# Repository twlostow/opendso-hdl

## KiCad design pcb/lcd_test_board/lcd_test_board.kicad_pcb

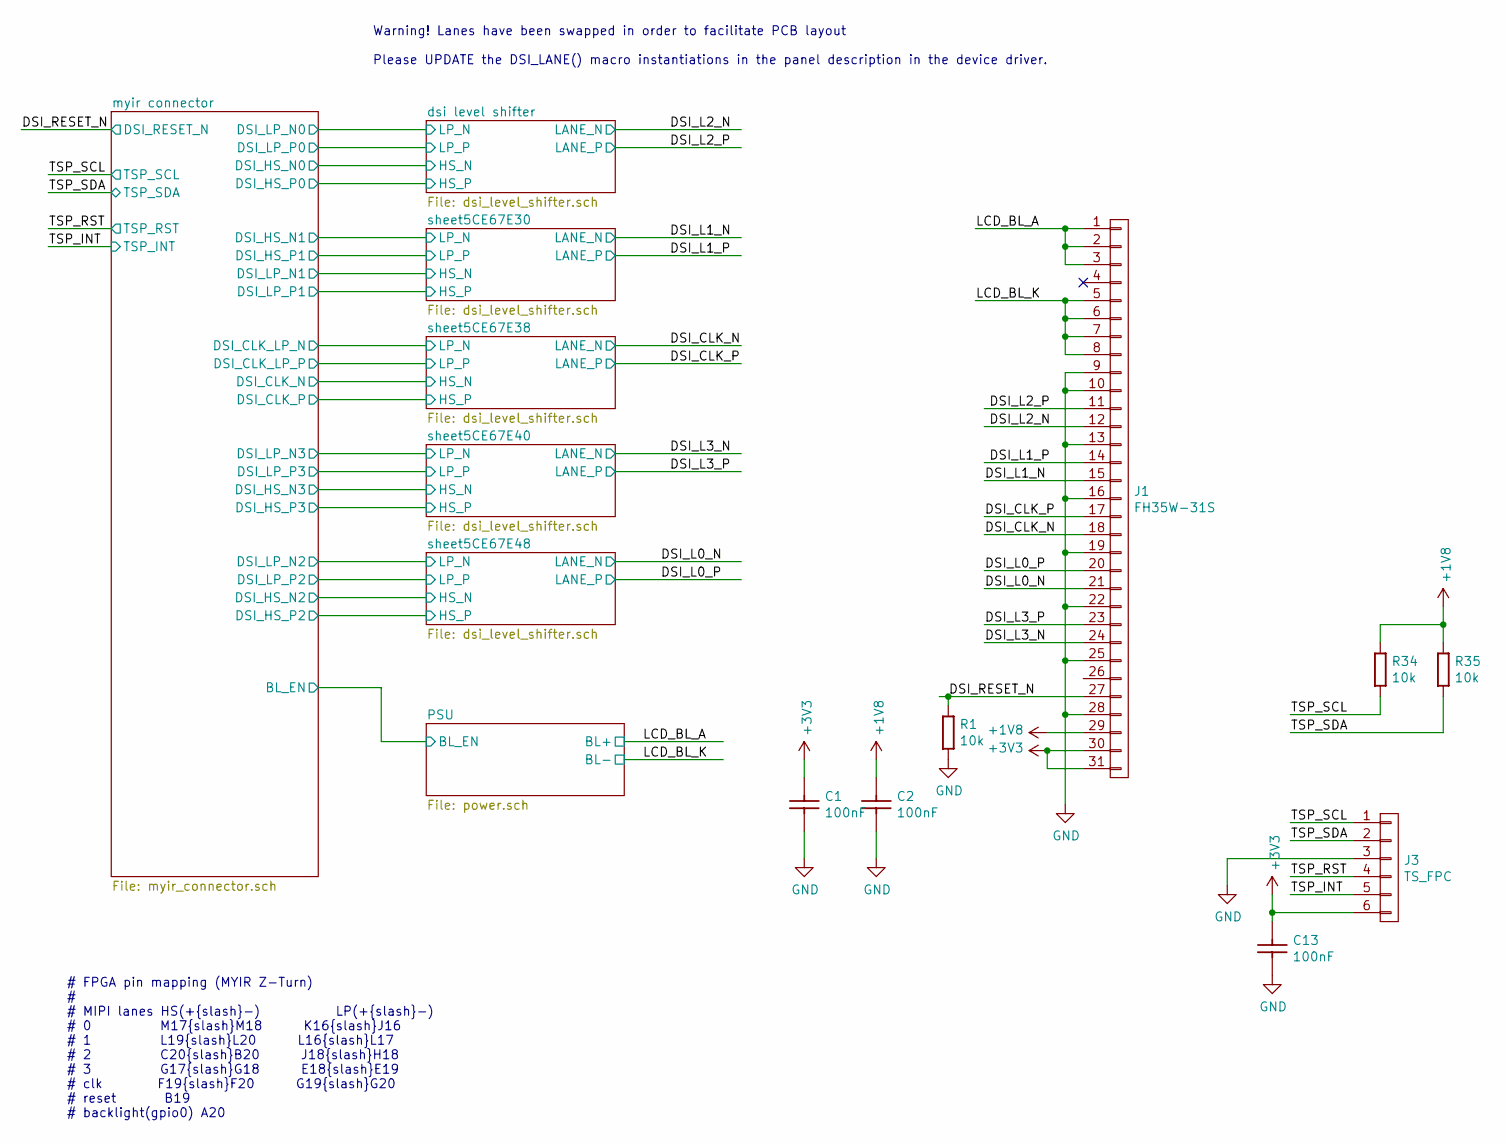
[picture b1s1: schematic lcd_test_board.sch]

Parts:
C1, C2, C13: CC0603_100NF_50V_10%_X5R; CAPC1608X87N; Voltage 50V; Tolerance ±10%; Part Number CC0603_100NF_50V_10%_X5R
J1: FH35W-31S
J3: TS_FPC; GT911_TS_FFC
R1, R34, R35: R0603_10K_1%_0.1W_100PPM; RESC1608X55N; Tolerance ±1%; Part Number R0603_10K_1%_0.1W_100PPM

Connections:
+1V8: C2.1, J1.29, R34.1, R35.1; also elsewhere on the board
+3V3: C1.1, C13.1, J1.30, J1.31, J3.6; also elsewhere on the board
/DSI_CLK_N: J1.18; also elsewhere on the board
/DSI_CLK_P: J1.17; also elsewhere on the board
/DSI_L0_N: J1.21; also elsewhere on the board
/DSI_L0_P: J1.20; also elsewhere on the board
/DSI_L1_N: J1.15; also elsewhere on the board
/DSI_L1_P: J1.14; also elsewhere on the board
/DSI_L2_N: J1.12; also elsewhere on the board
/DSI_L2_P: J1.11; also elsewhere on the board
/DSI_L3_N: J1.24; also elsewhere on the board
/DSI_L3_P: J1.23; also elsewhere on the board
/DSI_RESET_N: J1.27, R1.1; also elsewhere on the board
/LCD_BL_A: J1.1, J1.2, J1.3; also elsewhere on the board
/LCD_BL_K: J1.5, J1.6, J1.7, J1.8; also elsewhere on the board
/TSP_INT: J3.5; also elsewhere on the board
/TSP_RST: J3.4; also elsewhere on the board
/TSP_SCL: J3.1, R34.2; also elsewhere on the board
/TSP_SDA: J3.2, R35.2; also elsewhere on the board
GND: C1.2, C2.2, C13.2, J1.9, J1.10, J1.13, J1.16, J1.19, J1.22, J1.25, J1.28, J3.3, R1.2; also elsewhere on the board

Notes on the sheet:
# FPGA pin mapping (MYIR Z-Turn) # # MIPI lanes HS(+{slash}-) LP(+{slash}-) # 0 M17{slash}M18 K16{slash}J16 # 1 L19{slash}L20 L16{slash}L17 # 2 C20{slash}B20 J18{slash}H18 # 3 G17{slash}G18 E18{slash}E19 # clk F19{slash}F20 G19{slash}G20 # reset B19 # backlight(gpio0) A20
Warning! Lanes have been swapped in order to facilitate PCB layout Please UPDATE the DSI_LANE() macro instantiations in the panel description in the device driver.

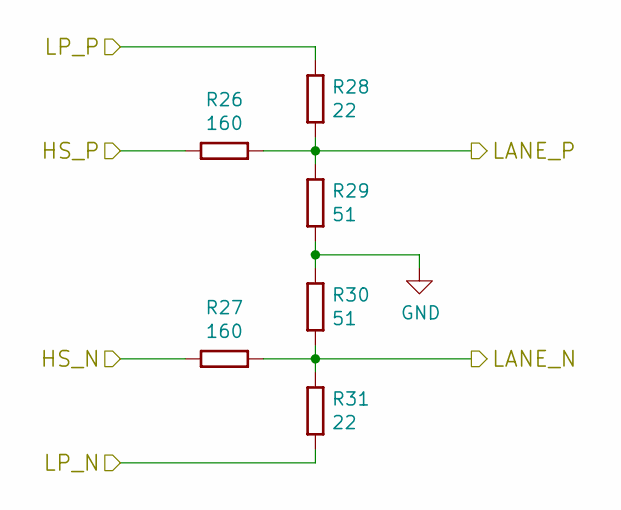
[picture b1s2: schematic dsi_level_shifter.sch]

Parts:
R2, R3: R0603_160R_1%_0.1W_100PPM; RESC1608X55N; Tolerance ±1%; Part Number R0603_160R_1%_0.1W_100PPM
R4, R7: R0603_22R_1%_0.1W_100PPM; RESC1608X55N; Tolerance ±1%; Part Number R0603_22R_1%_0.1W_100PPM
R5, R6: R0603_51R_1%_0.1W_100PPM; RESC1608X55N; Tolerance ±1%; Part Number R0603_51R_1%_0.1W_100PPM

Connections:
/DSI_HS_N0: R3.1; also elsewhere on the board
/DSI_HS_P0: R2.1; also elsewhere on the board
/DSI_L2_N: R3.2, R6.2, R7.1; also elsewhere on the board
/DSI_L2_P: R2.2, R4.2, R5.1; also elsewhere on the board
/DSI_LP_N0: R7.2; also elsewhere on the board
/DSI_LP_P0: R4.1; also elsewhere on the board
GND: R5.2, R6.1; also elsewhere on the board

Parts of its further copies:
R8, R9, R14, R15, R20, R21, R26, R27: R0603_160R_1%_0.1W_100PPM; RESC1608X55N; Tolerance ±1%; Part Number R0603_160R_1%_0.1W_100PPM
R10, R13, R16, R19, R22, R25, R28, R31: R0603_22R_1%_0.1W_100PPM; RESC1608X55N; Tolerance ±1%; Part Number R0603_22R_1%_0.1W_100PPM
R11, R12, R17, R18, R23, R24, R29, R30: R0603_51R_1%_0.1W_100PPM; RESC1608X55N; Tolerance ±1%; Part Number R0603_51R_1%_0.1W_100PPM

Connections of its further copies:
/DSI_CLK_LP_N: R19.2; also elsewhere on the board
/DSI_CLK_LP_P: R16.1; also elsewhere on the board
/DSI_CLK_N: R15.2, R18.2, R19.1; also elsewhere on the board
/DSI_CLK_N_1: R15.1; also elsewhere on the board
/DSI_CLK_P: R14.2, R16.2, R17.1; also elsewhere on the board
/DSI_CLK_P_1: R14.1; also elsewhere on the board
/DSI_HS_N1: R13.2; also elsewhere on the board
/DSI_HS_N2: R27.1; also elsewhere on the board
/DSI_HS_N3: R21.1; also elsewhere on the board
/DSI_HS_P1: R10.1; also elsewhere on the board
/DSI_HS_P2: R26.1; also elsewhere on the board
/DSI_HS_P3: R20.1; also elsewhere on the board
/DSI_L0_N: R27.2, R30.2, R31.1; also elsewhere on the board
/DSI_L0_P: R26.2, R28.2, R29.1; also elsewhere on the board
/DSI_L1_N: R9.2, R12.2, R13.1; also elsewhere on the board
/DSI_L1_P: R8.2, R10.2, R11.1; also elsewhere on the board
/DSI_L3_N: R21.2, R24.2, R25.1; also elsewhere on the board
/DSI_L3_P: R20.2, R22.2, R23.1; also elsewhere on the board
/DSI_LP_N1: R9.1; also elsewhere on the board
/DSI_LP_N2: R31.2; also elsewhere on the board
/DSI_LP_N3: R25.2; also elsewhere on the board
/DSI_LP_P1: R8.1; also elsewhere on the board
/DSI_LP_P2: R28.1; also elsewhere on the board
/DSI_LP_P3: R22.1; also elsewhere on the board
GND: R11.2, R12.1, R17.2, R18.1, R23.2, R24.1, R29.2, R30.1; also elsewhere on the board

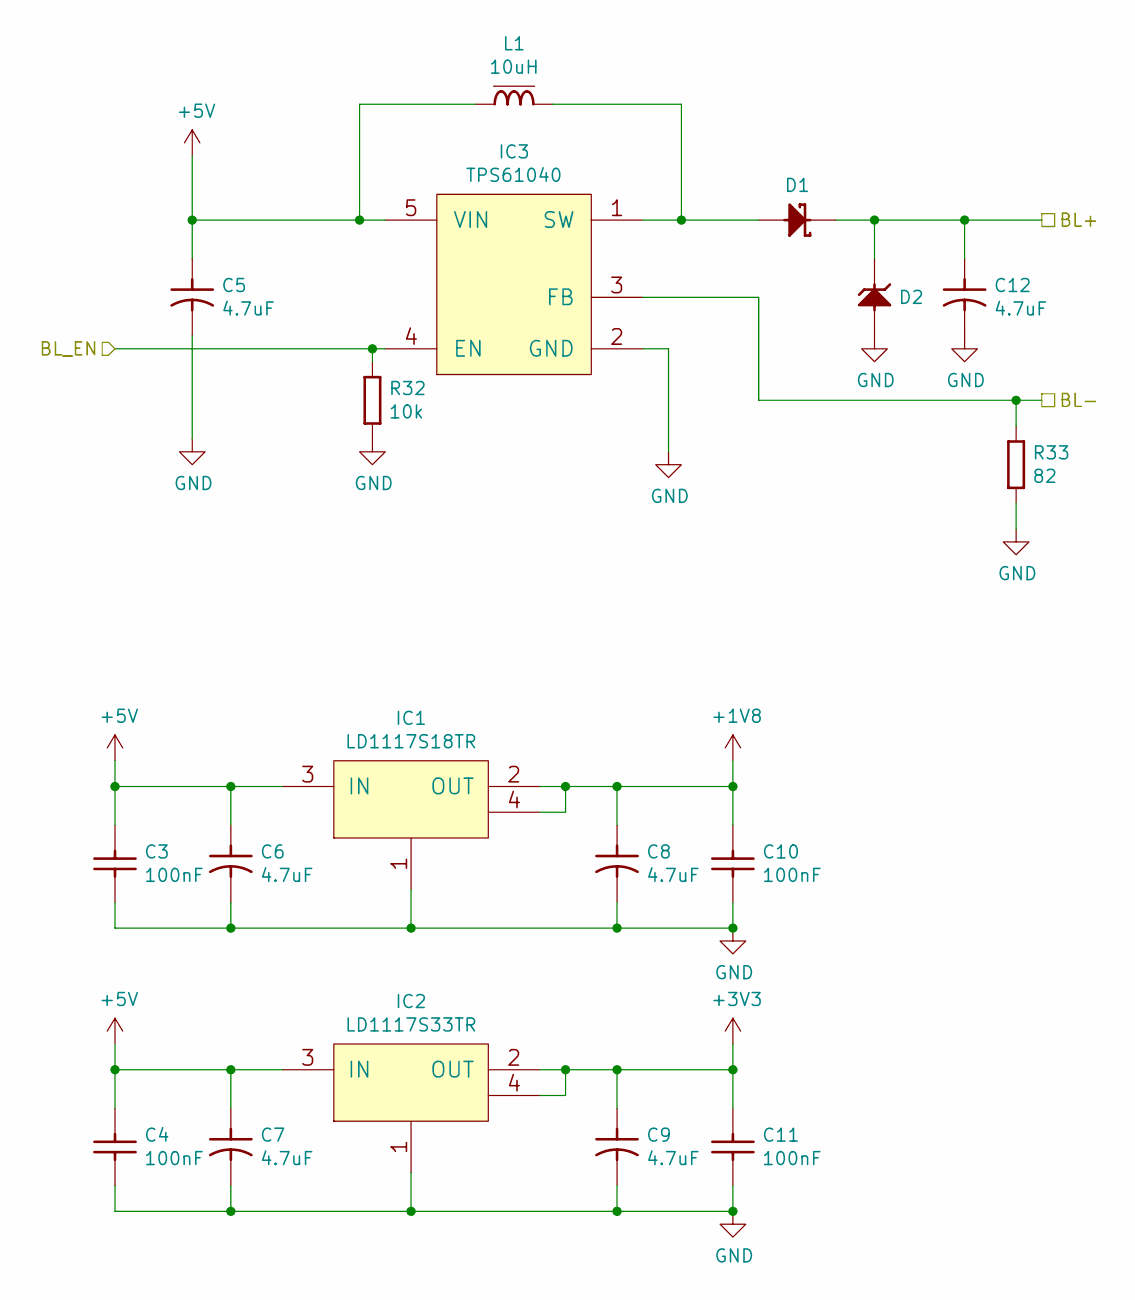
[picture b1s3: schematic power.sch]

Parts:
C3, C4, C10, C11: CC0603_100NF_50V_10%_X7R; CAPC1608X87N; Voltage 50V; Tolerance ±10%; Part Number CC0603_100NF_50V_10%_X7R
C5, C6, C7, C8, C9, C12: CTE3216-18_4.7UF_10V_10%_AVX_TPSA475K010T1400; CAPMP3216X180N; Voltage 10V; Tolerance ±10%; Part Number CTE3216-18_4.7UF_10V_10%_AVX_TPSA475K01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
D1: MBRM120LT1G; ONSEMI_POWERMITE; Voltage 20V; Part Number MBRM120LT1G
D2: BZG03C24; DIOM5326X230N; Voltage 24V; Part Number BZG03C24
IC1: LD1117S18TR; SOT230P700X180-4N; Part Number LD1117S18TR
IC2: LD1117S33TR; SOT230P700X180-4N; Part Number LD1117S18TR
IC3: TPS61041-; SOT95P280X90-5N
L1: IND_10UH_20%_TDK_VLCF5020-1; IND_TDK_VLCF5020-1; Tolerance ±20%; Part Number IND_10UH_20%_TDK_VLCF5020-1
R32: R0603_10K_1%_0.1W_100PPM; RESC1608X55N; Tolerance ±1%; Part Number R0603_10K_1%_0.1W_100PPM
R33: R0603_82R_1%_0.1W_100PPM; RESC1608X55N; Tolerance ±1%; Part Number R0603_82R_1%_0.1W_100PPM

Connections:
+1V8: C8.1, C10.1, IC1.2 (OUT), IC1.4 (OUT); also elsewhere on the board
+3V3: C9.1, C11.1, IC2.2 (OUT), IC2.4 (OUT); also elsewhere on the board
+5V: C3.1, C4.1, C5.1, C6.1, C7.1, IC1.3 (IN), IC2.3 (IN), IC3.5 (VIN), L1.1; also elsewhere on the board
/BL_EN: IC3.4 (EN), R32.1; also elsewhere on the board
/LCD_BL_A: C12.1, D1.1 (C), D2.1 (C); also elsewhere on the board
/LCD_BL_K: IC3.3 (FB), R33.1; also elsewhere on the board
GND: C3.2, C4.2, C5.2, C6.2, C7.2, C8.2, C9.2, C10.2, C11.2, C12.2, D2.2 (A), IC1.1 (GND), IC2.1 (GND), IC3.2 (GND), R32.2, R33.2; also elsewhere on the board
unnamed: D1.2 (A), IC3.1 (SW), L1.2

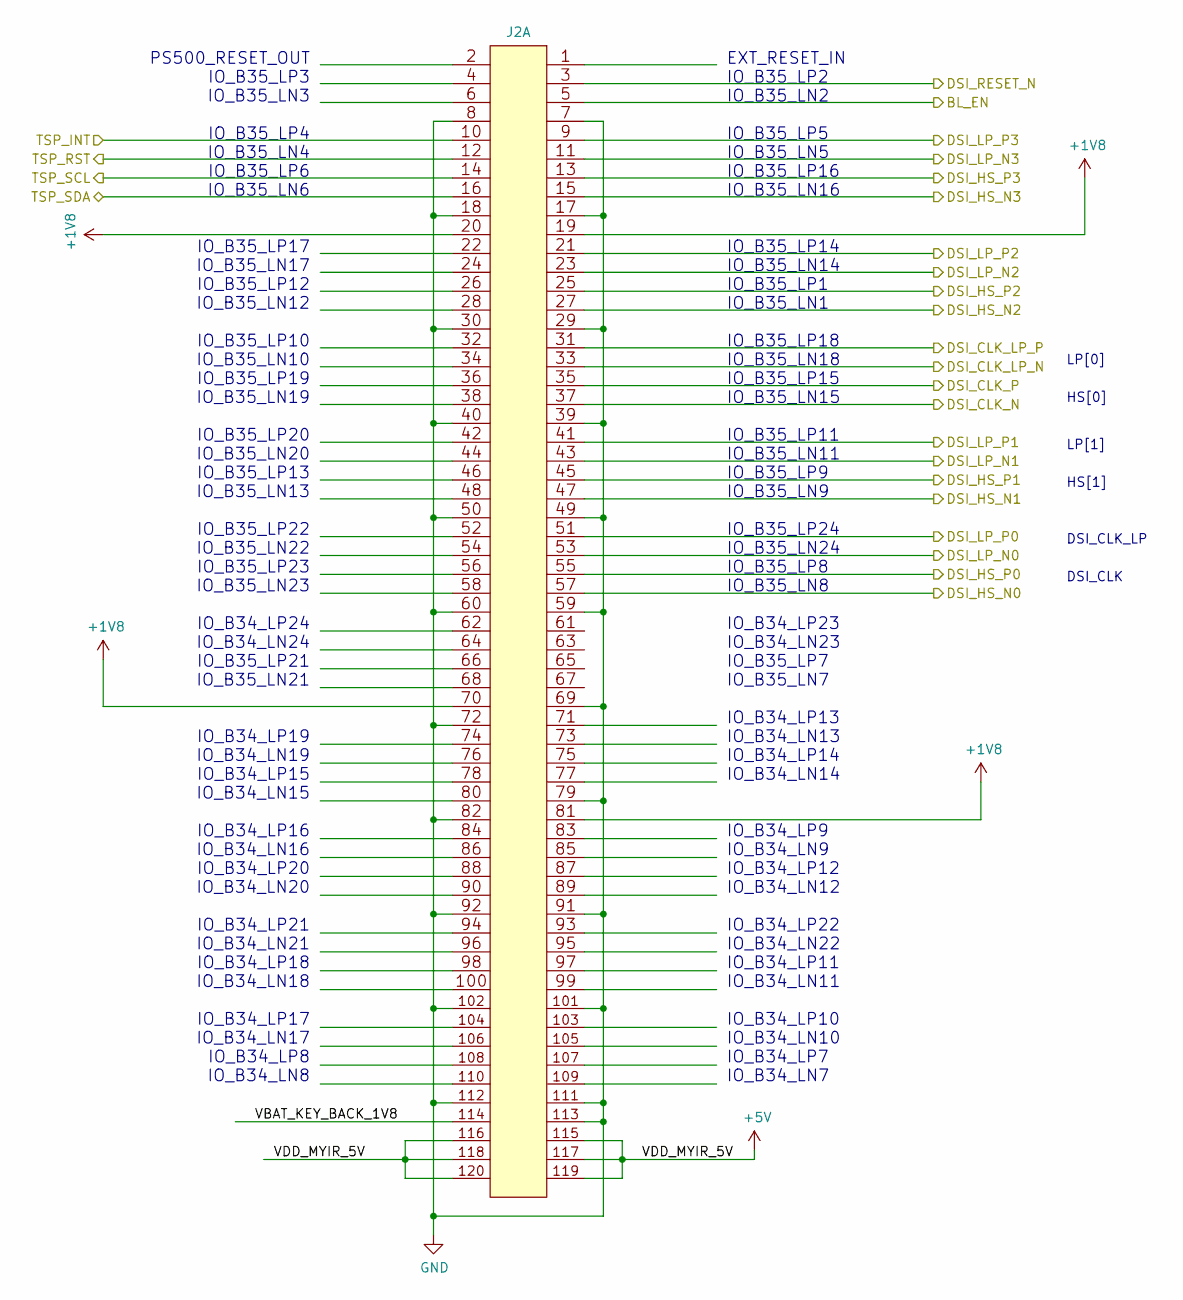
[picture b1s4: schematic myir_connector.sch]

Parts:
J2: SAMTEC_BTH-060-01-L-D-A; Part Number SAMTEC_QSH-060-01-L-D-A

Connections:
+1V8: J2.19, J2.20, J2.70, J2.81; also elsewhere on the board
+5V: J2.115, J2.116, J2.117, J2.118, J2.119, J2.120; also elsewhere on the board
/BL_EN: J2.5; also elsewhere on the board
/DSI_CLK_LP_N: J2.33; also elsewhere on the board
/DSI_CLK_LP_P: J2.31; also elsewhere on the board
/DSI_CLK_N_1: J2.37; also elsewhere on the board
/DSI_CLK_P_1: J2.35; also elsewhere on the board
/DSI_HS_N0: J2.57; also elsewhere on the board
/DSI_HS_N1: J2.47; also elsewhere on the board
/DSI_HS_N2: J2.27; also elsewhere on the board
/DSI_HS_N3: J2.15; also elsewhere on the board
/DSI_HS_P0: J2.55; also elsewhere on the board
/DSI_HS_P1: J2.45; also elsewhere on the board
/DSI_HS_P2: J2.25; also elsewhere on the board
/DSI_HS_P3: J2.13; also elsewhere on the board
/DSI_LP_N0: J2.53; also elsewhere on the board
/DSI_LP_N1: J2.43; also elsewhere on the board
/DSI_LP_N2: J2.23; also elsewhere on the board
/DSI_LP_N3: J2.11; also elsewhere on the board
/DSI_LP_P0: J2.51; also elsewhere on the board
/DSI_LP_P1: J2.41; also elsewhere on the board
/DSI_LP_P2: J2.21; also elsewhere on the board
/DSI_LP_P3: J2.9; also elsewhere on the board
/DSI_RESET_N: J2.3; also elsewhere on the board
/TSP_INT: J2.10; also elsewhere on the board
/TSP_RST: J2.12; also elsewhere on the board
/TSP_SCL: J2.14; also elsewhere on the board
/TSP_SDA: J2.16; also elsewhere on the board
GND: J2.7, J2.8, J2.17, J2.18, J2.29, J2.30, J2.39, J2.40, J2.49, J2.50, J2.59, J2.60, J2.69, J2.72, J2.79, J2.82, J2.91, J2.92, J2.101, J2.102, J2.111, J2.112, J2.113; also elsewhere on the board

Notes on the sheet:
DSI_CLK
DSI_CLK_LP
EXT_RESET_IN IO_B35_LP2 IO_B35_LN2 IO_B35_LP5 IO_B35_LN5 IO_B35_LP16 IO_B35_LN16 IO_B35_LP14 IO_B35_LN14 IO_B35_LP1 IO_B35_LN1 IO_B35_LP18 IO_B35_LN18 IO_B35_LP15 IO_B35_LN15 IO_B35_LP11 IO_B35_LN11 IO_B35_LP9 IO_B35_LN9 IO_B35_LP24 IO_B35_LN24 IO_B35_LP8 IO_B35_LN8 IO_B34_LP23 IO_B34_LN23 IO_B35_L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
PS500_RESET_OUT IO_B35_LP3 IO_B35_LN3 IO_B35_LP4 IO_B35_LN4 IO_B35_LP6 IO_B35_LN6 IO_B35_LP17 IO_B35_LN17 IO_B35_LP12 IO_B35_LN12 IO_B35_LP10 IO_B35_LN10 IO_B35_LP19 IO_B35_LN19 IO_B35_LP20 IO_B35_LN20 IO_B35_LP13 IO_B35_LN13 IO_B35_LP22 IO_B35_LN22 IO_B35_LP23 IO_B35_LN23 IO_B34_LP24 IO_B34_LN24 I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
LP[1]
HS[1]
LP[0]
HS[0]

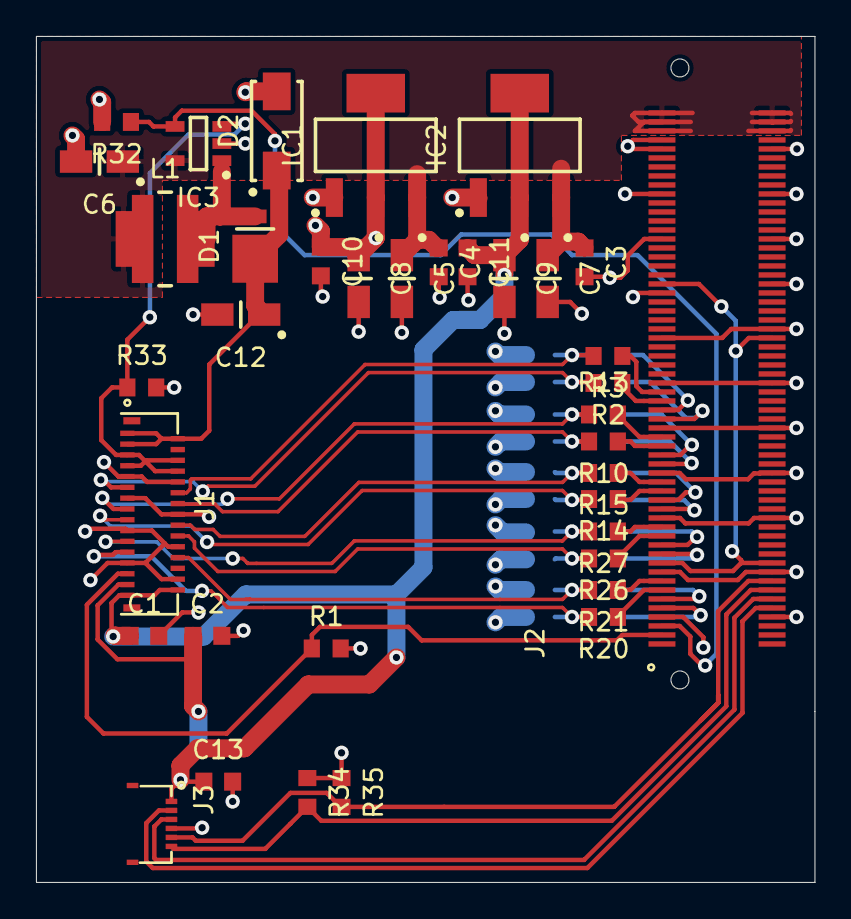
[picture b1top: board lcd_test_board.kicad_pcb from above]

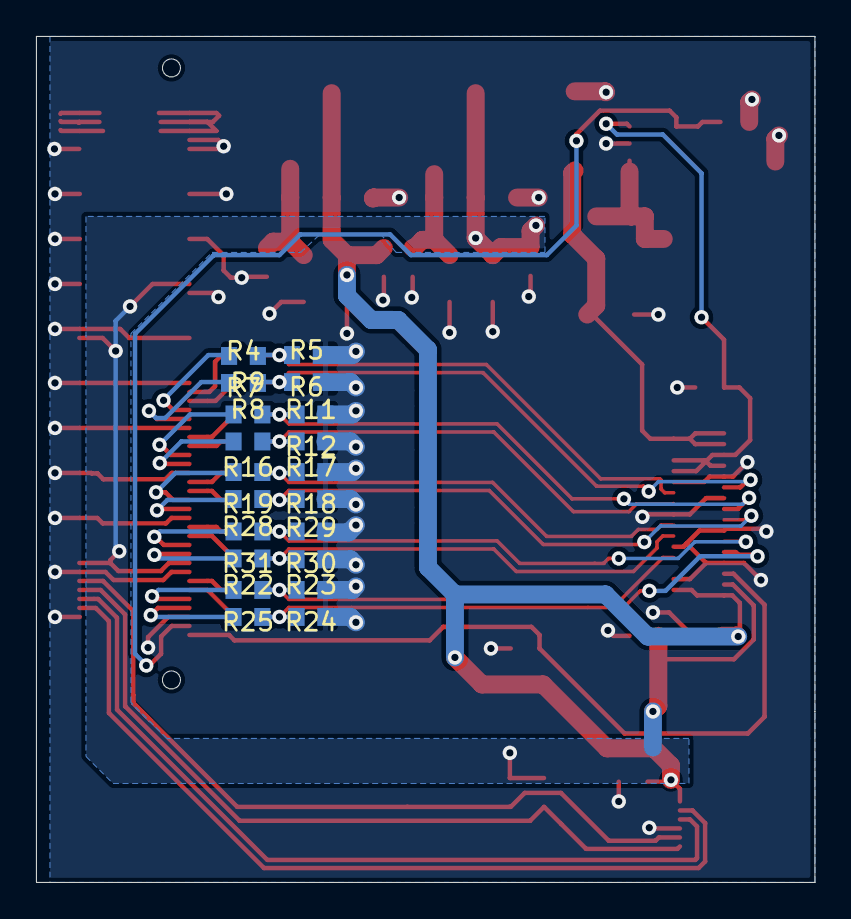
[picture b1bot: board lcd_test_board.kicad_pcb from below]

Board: 2 copper layers, 43.2 x 47.0 mm, 57 parts (20 on the bottom side), 43 nets.

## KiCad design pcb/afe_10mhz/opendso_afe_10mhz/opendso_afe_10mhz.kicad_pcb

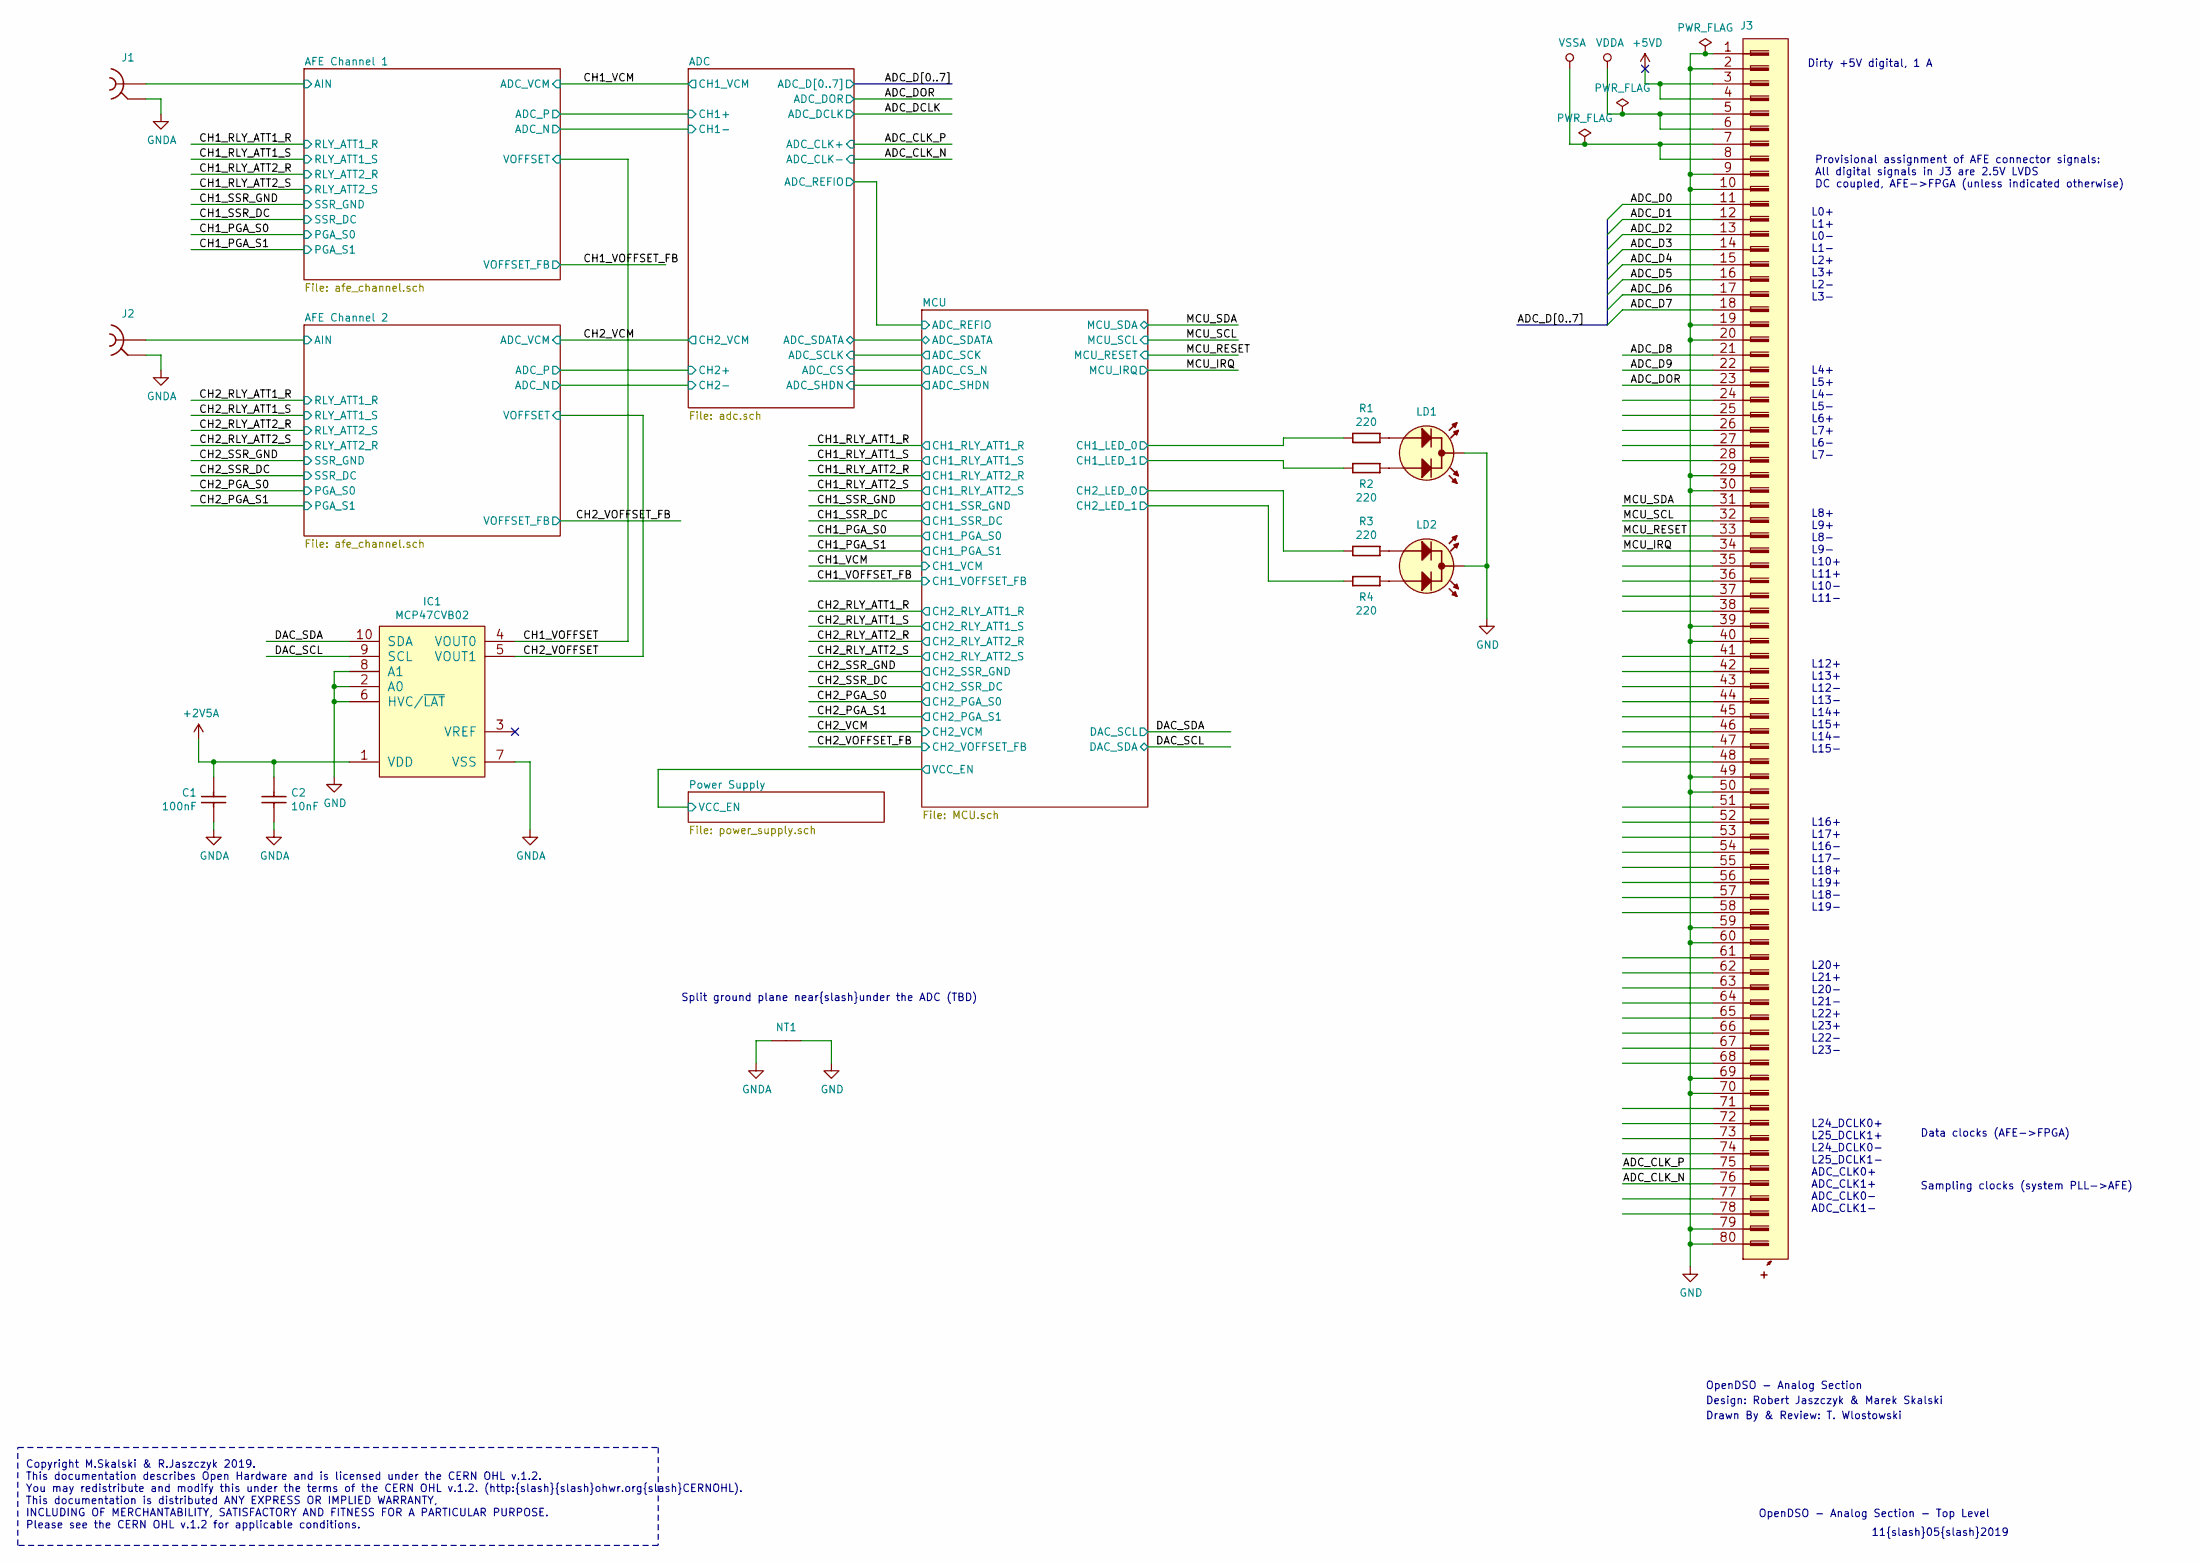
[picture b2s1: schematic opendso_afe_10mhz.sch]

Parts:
C1: CC0603_100NF_50V_10%_X7R; CAPC1608X87N; Voltage 50V; Tolerance ±10%; Part Number CC0603_100NF_50V_10%_X7R
C2: CC0603_10NF_50V_5%_C0G; CAPC1608X87N; Voltage 50V; Tolerance ±5%; Part Number CC0603_10NF_50V_5%_C0G
IC1: MCP47CVB02; SOP65P490X110-8N; Part Number MCP47CVB02
J1, J2: SAMTEC_HDBNC-J-P-GN-ST-TH1; BNC_TEConnectivity_1478204_Vertical; Part Number SAMTEC_HDBNC-J-P-GN-ST-TH1
J3: SAMTEC_LSS-140-01-L-DV-A; Part Number SAMTEC_LSS-140-01-L-DV-A
LD1, LD2: LED_DIALIGHT_550-3509F; Part Number LED_DIALIGHT_550-3509F
NT1: Net_Tie_2; Net Tie 2; Part Number Net_Tie_2
R1, R2, R3, R4: R0603_220R_1%_0.1W_100PPM; RESC1608X55N; Tolerance ±1%; Part Number R0603_220R_1%_0.1W_100PPM

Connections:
+2V5A: C1.2, C2.2, IC1.1 (VDD); also elsewhere on the board
+5VD: J3.3, J3.4; also elsewhere on the board
/ADC_CLK_N: J3.76; also elsewhere on the board
/ADC_CLK_P: J3.75; also elsewhere on the board
/ADC_D0: J3.11; also elsewhere on the board
/ADC_D1: J3.12; also elsewhere on the board
/ADC_D2: J3.13; also elsewhere on the board
/ADC_D3: J3.14; also elsewhere on the board
/ADC_D4: J3.15; also elsewhere on the board
/ADC_D5: J3.16; also elsewhere on the board
/ADC_D6: J3.17; also elsewhere on the board
/ADC_D7: J3.18; also elsewhere on the board
/ADC_DOR: J3.23; also elsewhere on the board
/AIN: J2.1; also elsewhere on the board
/AIN_1: J1.1; also elsewhere on the board
/CH1_LED_0: R1.1; also elsewhere on the board
/CH1_LED_1: R2.1; also elsewhere on the board
/CH1_VOFFSET: IC1.4 (VOUT0); also elsewhere on the board
/CH2_LED_0: R3.1; also elsewhere on the board
/CH2_LED_1: R4.1; also elsewhere on the board
/CH2_VOFFSET: IC1.5 (VOUT1); also elsewhere on the board
/DAC_SCL: IC1.9 (SCL); also elsewhere on the board
/DAC_SDA: IC1.10 (SDA); also elsewhere on the board
/MCU_IRQ: J3.34; also elsewhere on the board
/MCU_RESET: J3.33; also elsewhere on the board
/MCU_SCL: J3.32; also elsewhere on the board
/MCU_SDA: J3.31; also elsewhere on the board
unnamed: LD1.1 (AR), R1.2
unnamed: LD1.3 (AG), R2.2
unnamed: LD2.1 (AR), R3.2
unnamed: LD2.3 (AG), R4.2
VDDA: J3.5, J3.6; also elsewhere on the board
VSSA: J3.7, J3.8; also elsewhere on the board

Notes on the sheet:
OpenDSO - Analog Section - Top Level
11{slash}05{slash}2019
Design: Robert Jaszczyk & Marek Skalski
OpenDSO - Analog Section
Drawn By & Review: T. Wlostowski
L0+ L1+ L0- L1- L2+ L3+ L2- L3-
Provisional assignment of AFE connector signals: All digital signals in J3 are 2.5V LVDS DC coupled, AFE->FPGA (unless indicated otherwise)
Copyright M.Skalski & R.Jaszczyk 2019. This documentation describes Open Hardware and is licensed under the CERN OHL v.1.2. You may redistribute and modify this under the terms of the CERN OHL v.1.2. (http:{slash}{slash}ohwr.org{slash}CERNOHL). This documentation is distributed ANY EXPRESS OR IMPLI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
L4+ L5+ L4- L5- L6+ L7+ L6- L7-
L8+ L9+ L8- L9- L10+ L11+ L10- L11-
L12+ L13+ L12- L13- L14+ L15+ L14- L15-
L16+ L17+ L16- L17- L18+ L19+ L18- L19-
L20+ L21+ L20- L21- L22+ L23+ L22- L23-
L24_DCLK0+ L25_DCLK1+ L24_DCLK0- L25_DCLK1- ADC_CLK0+ ADC_CLK1+ ADC_CLK0- ADC_CLK1-
Split ground plane near{slash}under the ADC (TBD)
Data clocks (AFE->FPGA)
Sampling clocks (system PLL->AFE)
Dirty +5V digital, 1 A

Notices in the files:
parts and their libraries:
This work is licensed under the Creative Commons CC-BY-SA 4.0 License. To the extent that circuit schematics that use Licensed Material can be considered to be ‘Adapted Material’, then the copyright holder waives article 3.b of the license with respect to these schematics.
